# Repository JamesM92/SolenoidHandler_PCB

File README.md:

# SolenoidHandlerBoard
Board to help handle cable management, and EMF handler

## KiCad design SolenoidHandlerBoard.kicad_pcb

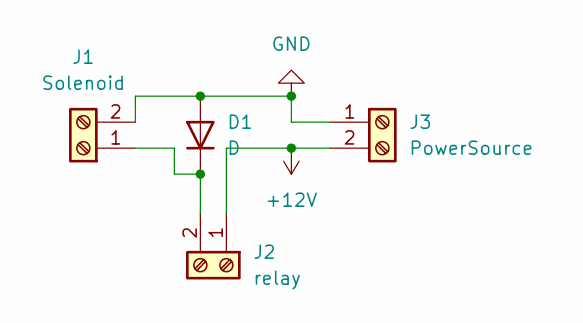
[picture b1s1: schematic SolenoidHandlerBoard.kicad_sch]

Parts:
D1: D; D_DO-34_SOD68_P7.62mm_Horizontal
J1: Solenoid; TerminalBlock_Phoenix_PT-1,5-2-5.0-H_1x02_P5.00mm_Horizontal
J2: relay; TerminalBlock_Phoenix_PT-1,5-2-5.0-H_1x02_P5.00mm_Horizontal
J3: PowerSource; TerminalBlock_Phoenix_PT-1,5-2-5.0-H_1x02_P5.00mm_Horizontal

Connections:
+12V: J2.1, J3.2
GND: D1.2 (A), J1.2, J3.1
unnamed: D1.1 (K), J1.1, J2.2

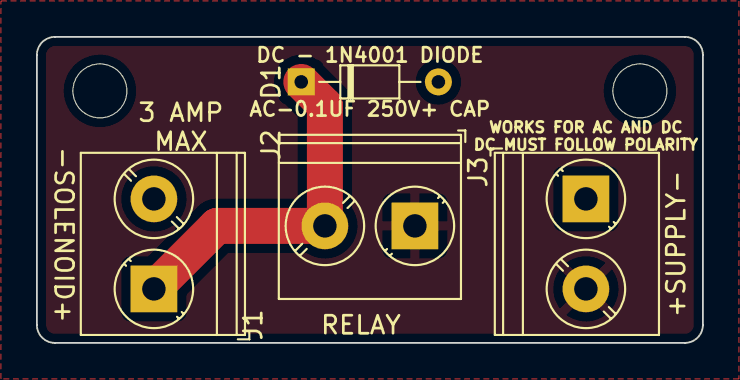
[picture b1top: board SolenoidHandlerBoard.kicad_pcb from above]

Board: 2 copper layers, 37.0 x 17.0 mm, 4 parts (0 on the bottom side), 3 nets.

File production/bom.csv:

Designator,Footprint,Quantity,Value,LCSC Part #
D1,D_DO-34_SOD68_P7.62mm_Horizontal,1,D,
J2,"TerminalBlock_Phoenix_PT-1,5-2-5.0-H_1x02_P5.00mm_Horizontal",1,relay,
J3,"TerminalBlock_Phoenix_PT-1,5-2-5.0-H_1x02_P5.00mm_Horizontal",1,PowerSource,
J1,"TerminalBlock_Phoenix_PT-1,5-2-5.0-H_1x02_P5.00mm_Horizontal",1,Solenoid,
